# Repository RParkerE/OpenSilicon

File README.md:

# OpenSilicon

Open-source semiconductor fabrication for the home lab. Build and operate IC fabrication equipment with detailed guides, CAD files, firmware, and process recipes.

## About

OpenSilicon brings semiconductor fabrication capabilities into the home lab. This project provides comprehensive documentation, designs, and software for building functional IC fabrication equipment for research, education, and experimentation.

We are currently developing the alpha stage of the fabrication pipeline, targeting sub micron feature resolution across the complete process flow: spin coating, direct write lithography, metrology, oxidation, and physical vapor deposition (PVD).

## Status

**Alpha Stage - Active Development**

This is an early-stage project. All equipment designs and processes are works in progress and subject to change. Current development is running two parallel tracks:

**Metrology (FPM / R-FPM)**
- Working prototype complete
- Fourier Ptychographic Microscopy (FPM) and Reflective FPM (R-FPM) under active characterization

**Direct Write Lithography (405nm)**
- Laser control code and firmware complete
- Actively working on motion circuitry and positioning firmware
- Investigating voice coil actuators from blu-ray drive for fine positioning
- Separate 3-axis alignment tool in development

**Other Systems**
- Spin coating system
    - Prototype full assembly complete
    - TODO: Look into web socket connectivity issues
    - TODO: Add a resist fill method
- Oxidation furnace fabrication pipeline
- PVD deposition system integration
- Process characterization and documentation

Join us to help shape the project during these formative stages.

## Getting Started

### Prerequisites

- Basic electronics and mechanical assembly experience
- Interest in semiconductor fabrication and experimental work
- Familiarity with working safely with high temperatures and electrical systems
- 3D printer access (optional, for custom components)

### Next Steps

1. Review the documentation to understand the current state of each component
2. Check open issues to see what's being worked on
3. Start contributing - documentation, testing, and feedback are valuable at this stage

## Equipment in Development

| Equipment | Status | Notes |
|-----------|--------|-------|
| Spin Coater | In Progress | Open issues remain |
| FPM / R-FPM Metrology | Working Prototype | Active characterization |
| Direct Write Lithography | In Progress | Laser firmware complete; positioning and alignment in development |
| 3-Axis Alignment Tool | In Progress | Companion to lithography system |
| Oxidation Furnace | In Progress | Initial build phase |
| PVD Deposition System | In Progress | Initial build phase |

## License

OpenSilicon is licensed under the **GNU General Public License v3**. See [LICENSE](LICENSE) for details.

This project integrates components licensed under GPLv3. When using or modifying this project, you must:

- Provide source code to users
- License derivative works under GPLv3
- Include a copy of the license
- State significant changes made

## Contributing

We actively welcome contributions. This project is in its early stages, and input from the community is essential.

### Getting Started with Contributing

1. Check [open issues](../../issues) and [discussions](../../discussions)
2. Reach out with ideas or questions before starting major work
3. Submit pull requests for feedback and discussion

### Ways to Contribute

- Share feedback on design decisions and approaches
- Document your work and help build the knowledge base
- Report issues, problems, observations, and learnings
- Propose design changes or optimizations
- Contribute firmware, software, and design improvements
- Help characterize equipment performance

## Community

- **GitHub Discussions**: [Ask questions and discuss ideas](../../discussions)
- **Issues**: [Report bugs and suggest features](../../issues)
- **Email**: [parker.ellwanger@gmail.com](mailto:parker.ellwanger@gmail.com)

## Roadmap

- [ ] Complete FPM/R-FPM metrology characterization
- [ ] Complete lithography positioning system (voice coil + 3-axis alignment)
- [ ] Complete alpha stage (sub micron) for all equipment
- [ ] Finalize process procedures and characterization data
- [ ] Publish comprehensive build guides
- [ ] Establish baseline performance metrics
- [ ] Improve lithography system resolution to work with the Open PDKs at 130nm process

## Performance & Limitations

OpenSilicon is targeting:

- **Feature resolution**: sub micron (alpha stage)
- **Use case**: Research, education, and experimentation
- **Scale**: Small-batch processing
- **Goal**: Accessible home lab fabrication, not production

## Safety

**This project involves significant hazards.** Home semiconductor fabrication includes:

- High temperature operation (up to 1000°C+)
- High voltage electrical systems
- UV radiation exposure
- Chemical hazards

Users are responsible for understanding and mitigating these risks. Always follow safety procedures and never operate equipment unsupervised.

## Building from Source

All designs are provided in open formats. No proprietary software is required:

- **CAD Files**: STEP and STL formats
- **Firmware**: Open-source microcontroller code
- **Software**: Python and standard development tools

## Acknowledgments

OpenSilicon builds on research and contributions from the open-source hardware community and makers exploring accessible semiconductor fabrication.

## Disclaimer

Use of OpenSilicon designs and instructions is at your own risk. The authors assume no liability for injuries, property damage, or other consequences from assembly, operation, or misuse of equipment built from these designs.

## Support

If you find OpenSilicon interesting, star this repository, share your interests and expertise, contribute to development, and help improve documentation.

**Have questions?** [Start a discussion](../../discussions) or [email us](mailto:parker.ellwanger@gmail.com).

**Found an issue?** [Report it](../../issues/new).

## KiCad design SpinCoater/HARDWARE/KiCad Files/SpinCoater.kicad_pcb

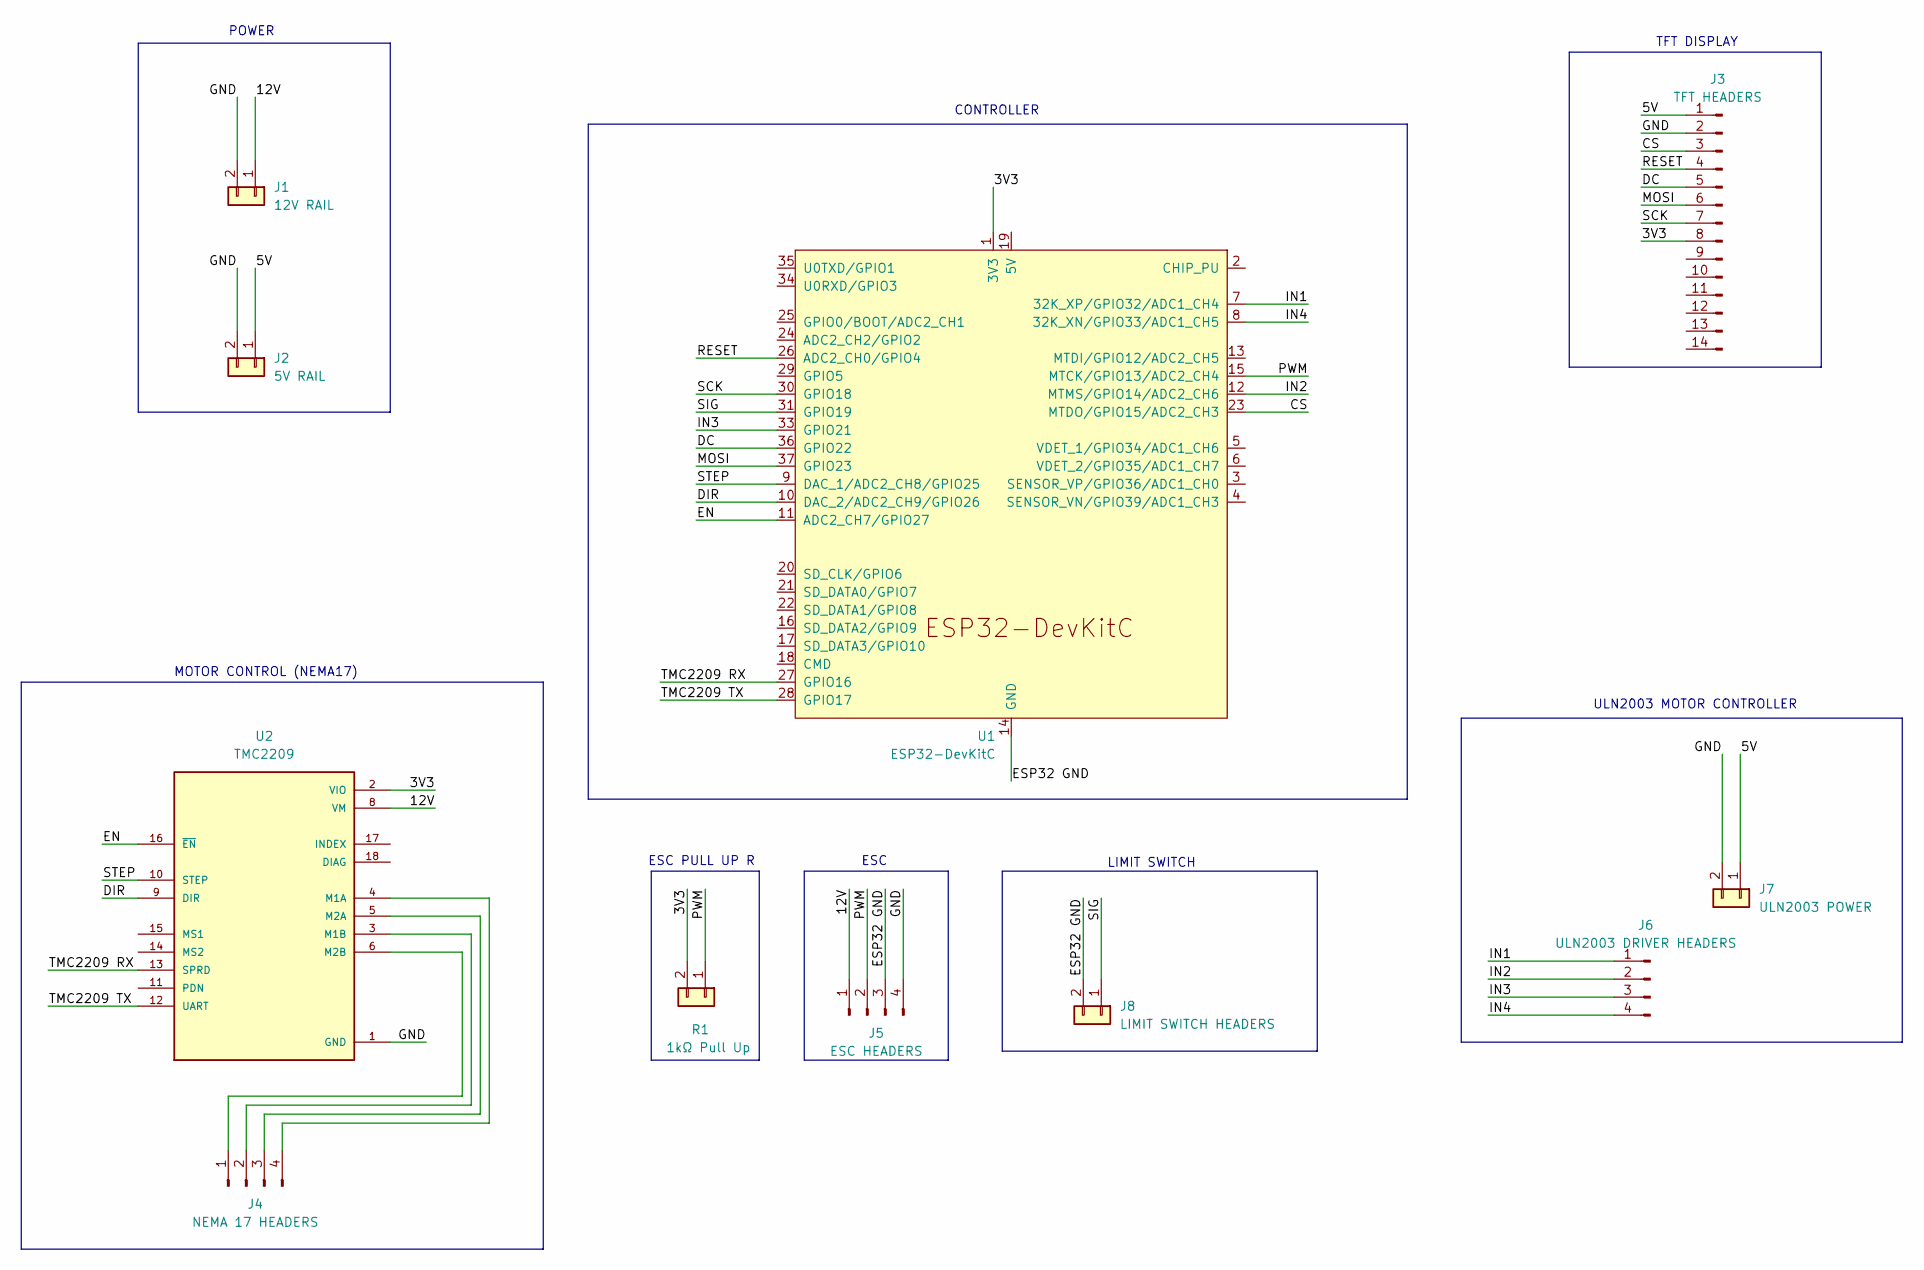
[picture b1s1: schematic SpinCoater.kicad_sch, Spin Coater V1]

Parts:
J1: 12V RAIL; PinHeader_1x02_P2.54mm_Vertical
J2: 5V RAIL; PinHeader_1x02_P2.54mm_Vertical
J3: TFT HEADERS; PinHeader_1x14_P2.54mm_Vertical
J4: NEMA 17 HEADERS; PinHeader_1x04_P2.54mm_Vertical
J5: ESC HEADERS; PinHeader_1x04_P2.54mm_Vertical
J6: ULN2003 DRIVER HEADERS; PinHeader_1x04_P2.54mm_Vertical
J7: ULN2003 POWER; PinHeader_1x02_P2.54mm_Vertical
J8: LIMIT SWITCH HEADERS; PinHeader_1x02_P2.54mm_Vertical
R1: 1kΩ Pull Up; R_Axial_DIN0207_L6.3mm_D2.5mm_P10.16mm_Horizontal
U1: ESP32-DevKitC
U2: TMC2209; MODULE_TMC2209_SILENTSTEPSTICK; PARTREV 1.20

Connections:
/3V3: J3.8, R1.2, U1.1 (3V3), U2.2 (VIO)
/5V: J2.1, J3.1, J7.1
/12V: J1.1, J5.1, U2.8 (VM)
/CS: J3.3, U1.23 (MTDO/GPIO15/ADC2_CH3)
/DC: J3.5, U1.36 (GPIO22)
/DIR: U1.10 (DAC_2/ADC2_CH9/GPIO26), U2.9 (DIR)
/EN: U1.11 (ADC2_CH7/GPIO27), U2.16 (~EN)
/ESP32 GND: J5.3, J8.2, U1.14 (GND), U1.32 (GND), U1.38 (GND)
/IN1: J6.1, U1.7 (32K_XP/GPIO32/ADC1_CH4)
/IN2: J6.2, U1.12 (MTMS/GPIO14/ADC2_CH6)
/IN3: J6.3, U1.33 (GPIO21)
/IN4: J6.4, U1.8 (32K_XN/GPIO33/ADC1_CH5)
/MOSI: J3.6, U1.37 (GPIO23)
/PWM: J5.2, R1.1, U1.15 (MTCK/GPIO13/ADC2_CH4)
/RESET: J3.4, U1.26 (ADC2_CH0/GPIO4)
/SCK: J3.7, U1.30 (GPIO18)
/SIG: J8.1, U1.31 (GPIO19)
/STEP: U1.9 (DAC_1/ADC2_CH8/GPIO25), U2.10 (STEP)
/TMC2209 RX: U1.27 (GPIO16), U2.13 (SPRD)
/TMC2209 TX: U1.28 (GPIO17), U2.12 (UART)
GND: J1.2, J2.2, J3.2, J5.4, J7.2, U2.1 (GND), U2.7 (GND)
unnamed: J4.1, U2.6 (M2B)
unnamed: J4.2, U2.3 (M1B)
unnamed: J4.3, U2.5 (M2A)
unnamed: J4.4, U2.4 (M1A)

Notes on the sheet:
MOTOR CONTROL (NEMA17)
ESC PULL UP R
ULN2003 MOTOR CONTROLLER
POWER
CONTROLLER
ESC
TFT DISPLAY
LIMIT SWITCH

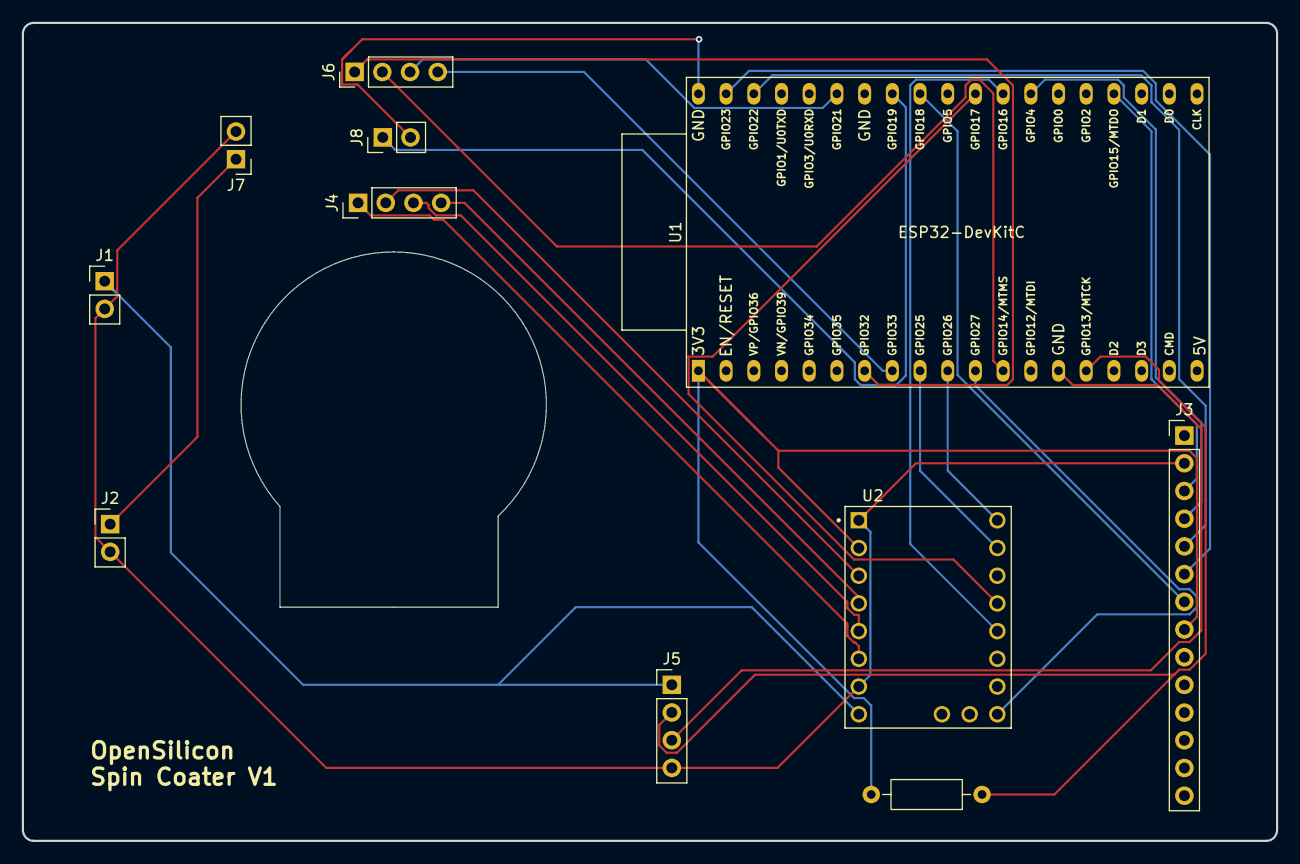
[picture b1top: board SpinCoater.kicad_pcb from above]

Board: 2 copper layers, 115.0 x 75.0 mm, 11 parts (0 on the bottom side), 25 nets.

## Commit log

2025-10-17 Initial README.md
2025-11-07 First working stage of SpinCoater Firmware
2025-11-09 Initial implementation of TFT display and homing sequence
2025-11-09 Update README to reflect updates
2025-11-10 Add properly calculated steps per uL and steps per mm
2025-11-13 TFT fix, and some minor adjustment to websocket connectivity
2025-11-15 Update README.md to start lithography build out
2025-11-19 Update README.md to reflect new targets and goals
2026-06-15 Create OPU.md
    Current pinout mappings for OPU
2026-06-30 Spin Coater V1 FIRMWARE FINAL
    - Updated and refactored firmware
    - Designed custom PCB and update KiCad files
    - (TODO) Update and finalize 3D printed housing and files
    - Included BOM
2026-06-30 Remove old files that were missed

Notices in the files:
README.md:
License: GPL v3
